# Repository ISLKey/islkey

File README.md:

# ISLKey

Access-control platform by **ISL Technologies** — ESP32-based door controllers with a
Windows flasher/commissioning tool and a companion mobile app.

## Repository layout

| Path | What it is | Stack |
|------|-----------|-------|
| `islkey-firmware/` | Door-controller firmware — 4 board targets (relay-board, devkit, ttgo, wt32-eth01). Inputs (exit/door/fire/tamper), relay-driven lock, cloud HMAC device-auth, NimBLE. | ESP32 / PlatformIO / Arduino |
| `islkey-flasher/`  | Desktop flasher + serial commissioning tool. Flashes merged full-flash images at `0x0`, assigns serials, writes WiFi/API config over serial. | Electron / Node.js |
| `islkey-app/`      | Companion door-access mobile app (NFC tap → resolve → unlock). | Flutter |
| `kicad/`           | KiCad 8 schematic for the TTGO controller (inputs, relay lock output, monitored fire link, backup power). | KiCad |
| `wordpress/`       | Drop-in integration notes for the isl-key WordPress plugin (device API / provisioning). | — |
| `make_wiring_diagram.py` | Generates the 4-sheet wiring/pinout PDF (`ISLKey-Wiring-Diagram.pdf`). | Python / matplotlib |
| `make_kicad_schematic.py` | Generates `kicad/ISLKey.kicad_sch` from source. | Python |

## Building

- **Firmware:** `cd islkey-firmware && python -m platformio run` (per-env in `platformio.ini`).
  After a rebuild, regenerate the merged images with `esptool merge_bin` (see below) — the
  flasher writes a **merged full-flash image at `0x0`**; a raw app image boot-loops the board.
- **Flasher:** `cd islkey-flasher && npm install && npm start` (or `npm run build` for the installer).
- **App:** `cd islkey-app && flutter pub get && flutter run`.

## Hardware notes

- On the **TTGO T-Display** target the TFT occupies GPIO 4/5/16/18/19/23, so door I/O is
  remapped: inputs GPIO 13/25/26/27, relays GPIO 32/33.
- The lock is switched via an **external opto-isolated relay module** (COM/NC), with a
  single **volt-free fire N/C contact in series** (hardware release, controller-independent)
  that is **opto-monitored to GPIO26** for fire detection + cable supervision. See `kicad/`
  and the wiring PDF.

## Not in this repo

Build artifacts (`.pio/`, `node_modules/`, Flutter `build/`, installer `dist/`) and
**operational secrets** — the per-device serial register / AP passwords (`islkey-flasher/serials/`)
and any real `.islkey` provisioning configs — are git-ignored.

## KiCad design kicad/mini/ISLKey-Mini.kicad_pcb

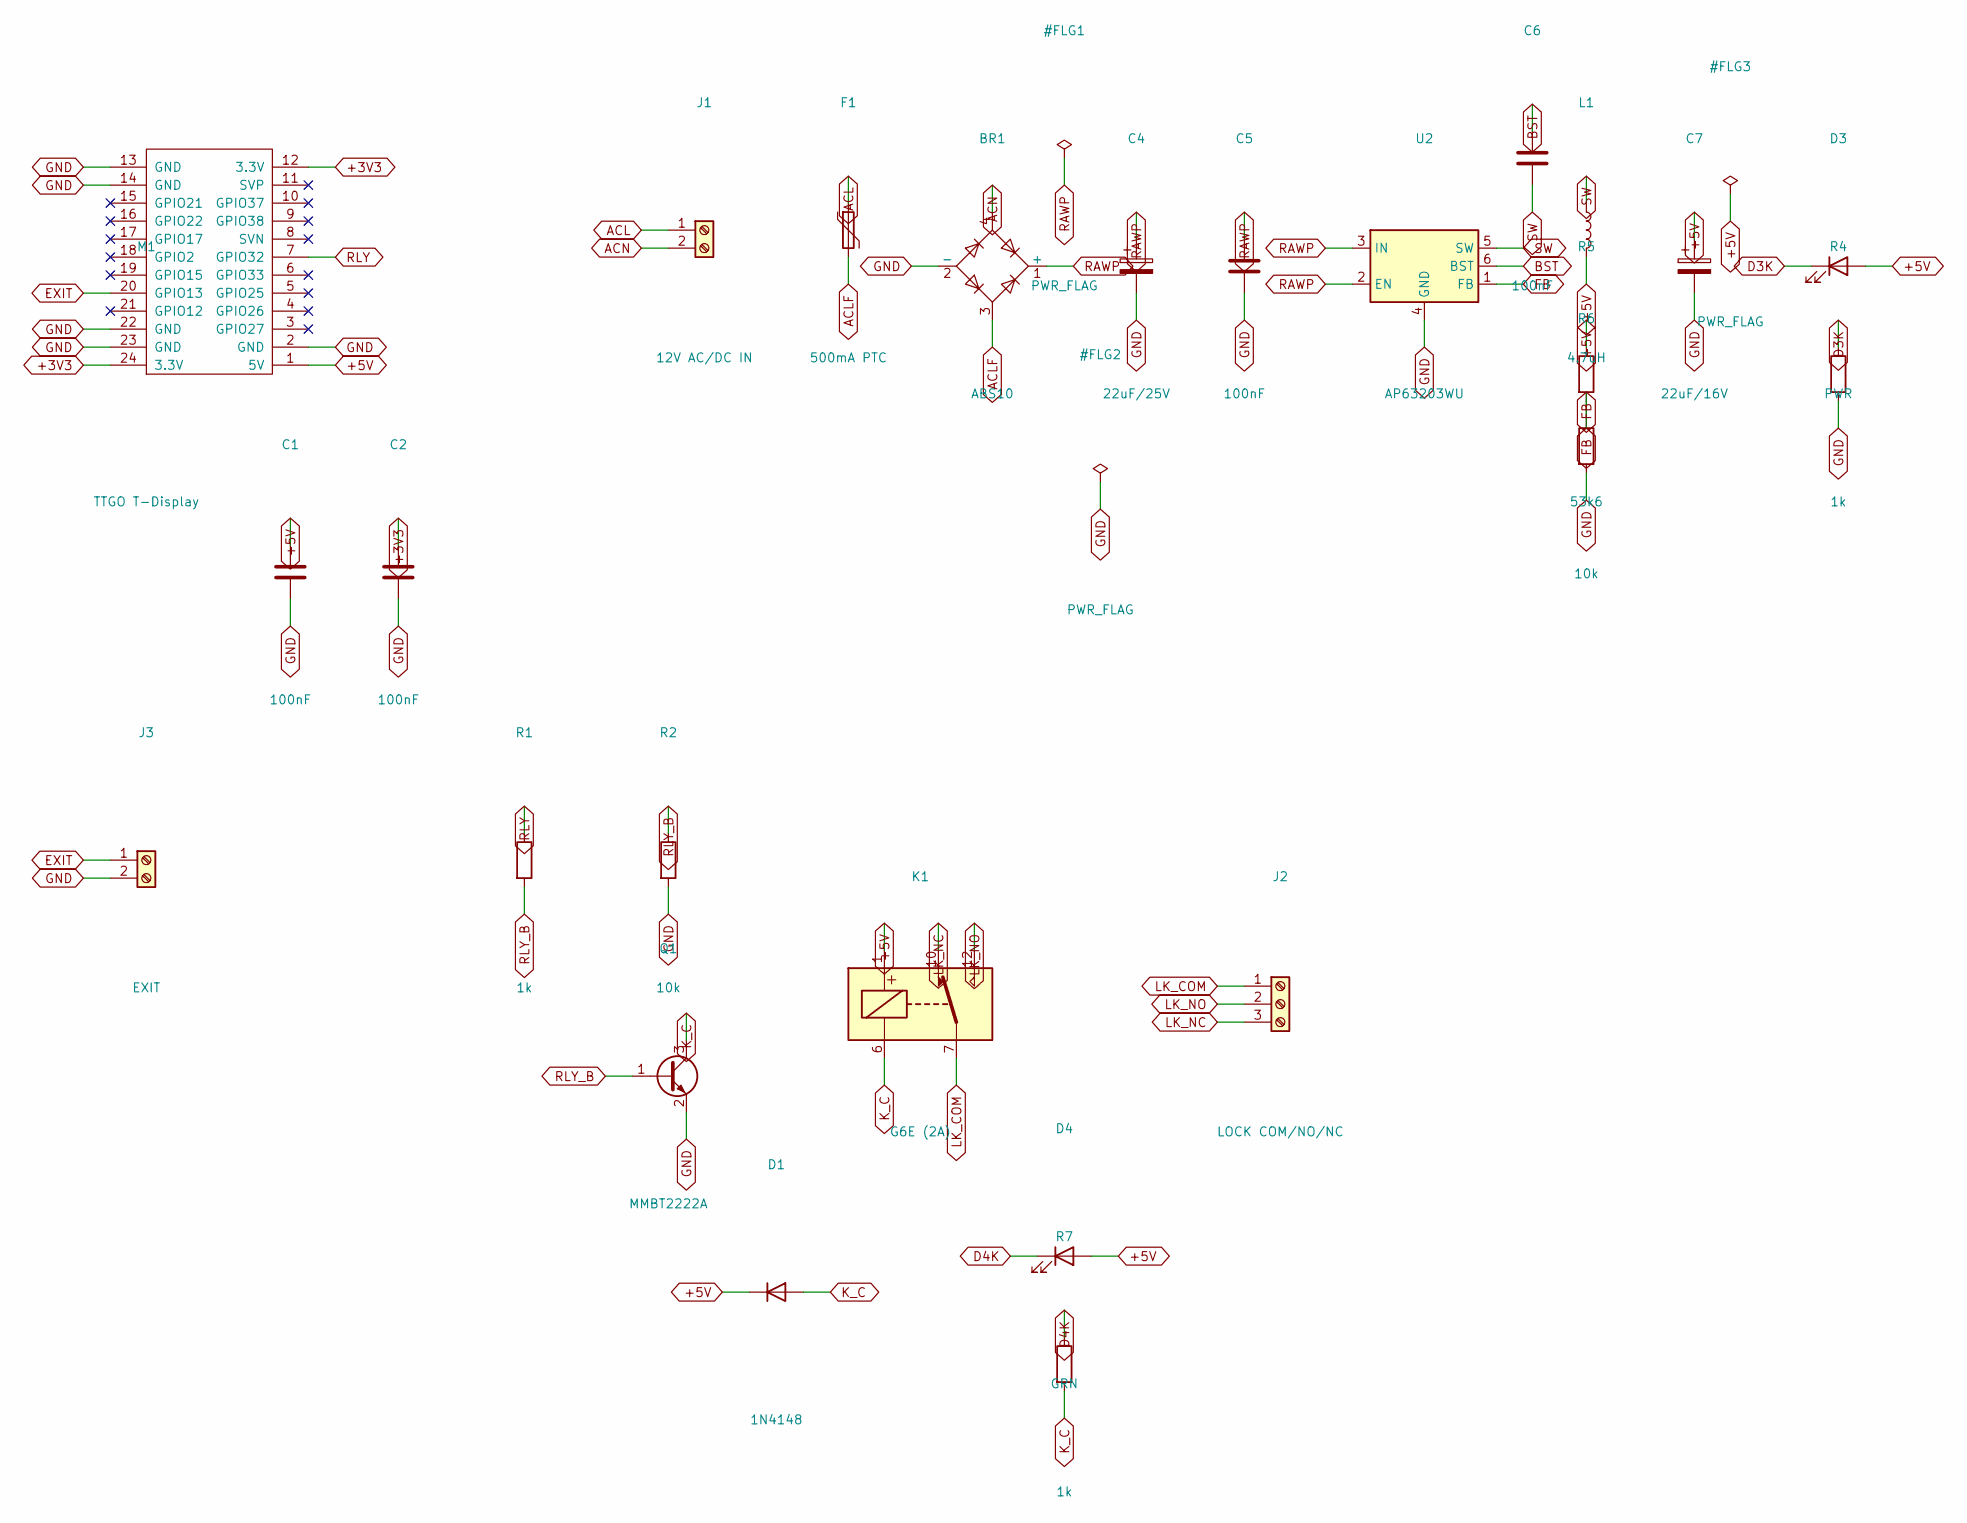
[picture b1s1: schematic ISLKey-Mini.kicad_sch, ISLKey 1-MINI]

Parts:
BR1: ABS10; Diode_Bridge_Diotec_ABS
C1, C2, C5, C6: 100nF; C_0805_2012Metric
C4: 22uF/25V; CP_Elec_6.3x5.3
C7: 22uF/16V; CP_Elec_6.3x5.3
D1: 1N4148; D_SOD-123
D3: PWR; LED_0805_2012Metric
D4: GRN; LED_0805_2012Metric
F1: 500mA PTC; Fuse_1812_4532Metric
J1: 12V AC/DC IN; TerminalBlock_Phoenix_PT-1,5-2-3.5-H_1x02_P3.50mm_Horizontal
J2: LOCK COM/NO/NC; TerminalBlock_Phoenix_PT-1,5-3-3.5-H_1x03_P3.50mm_Horizontal
J3: EXIT; TerminalBlock_Phoenix_PT-1,5-2-3.5-H_1x02_P3.50mm_Horizontal
K1: G6E (2A); Relay_SPDT_Omron_G6E
L1: 4.7uH; L_6.3x6.3_H3
M1: TTGO T-Display; TTGO_ESP32_TDisplay_v1.1
Q1: MMBT2222A; SOT-23
R1, R4, R7: 1k; R_0805_2012Metric
R2, R6: 10k; R_0805_2012Metric
R5: 53k6; R_0805_2012Metric
U2: AP63203WU; TSOT-23-6

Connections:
+3V3: C2.1, M1.12 (3.3V), M1.24 (3.3V)
+5V: C1.1, C7.1, D1.1 (K), D3.2 (A), D4.2 (A), K1.1, L1.2, M1.1 (5V), R5.1
ACL: F1.1, J1.1
ACLF: BR1.3, F1.2
ACN: BR1.4, J1.2
BST: C6.1, U2.6 (BST)
D3K: D3.1 (K), R4.1
D4K: D4.1 (K), R7.1
EXIT: J3.1, M1.20 (GPIO13)
FB: R5.2, R6.1, U2.1 (FB)
GND: BR1.2 (-), C1.2, C2.2, C4.2, C5.2, C7.2, J3.2, M1.2 (GND), M1.13 (GND), M1.14 (GND), M1.22 (GND), M1.23 (GND), Q1.2 (E), R2.2, R4.2, R6.2, U2.4 (GND)
K_C: D1.2 (A), K1.6, Q1.3 (C), R7.2
LK_COM: J2.1, K1.7
LK_NC: J2.3, K1.10
LK_NO: J2.2, K1.12
RAWP: BR1.1 (+), C4.1, C5.1, U2.2 (EN), U2.3 (IN)
RLY: M1.7 (GPIO32), R1.1
RLY_B: Q1.1 (B), R1.2, R2.1
SW: C6.2, L1.1, U2.5 (SW)

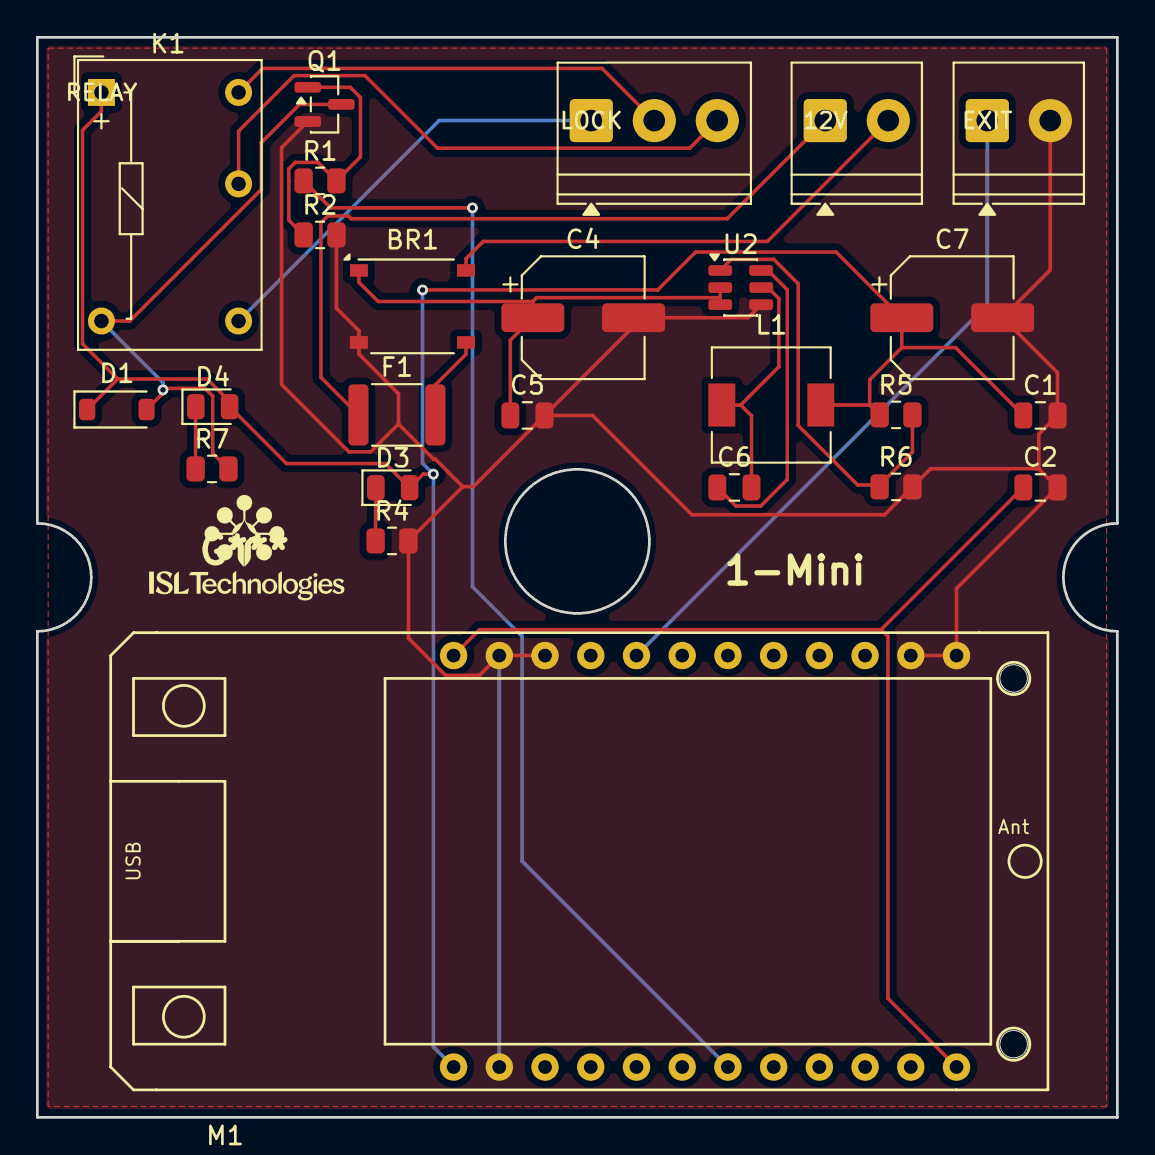
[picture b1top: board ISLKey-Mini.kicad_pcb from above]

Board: 2 copper layers, 60.0 x 60.0 mm, 25 parts (0 on the bottom side), 19 nets.

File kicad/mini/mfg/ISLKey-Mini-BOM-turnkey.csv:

Item,Refs,Qty,Value,Footprint,Type,Manufacturer,MPN,Distributor,Notes
1,"R1,R4,R7",3,1k,R_0805,SMD,Yageo,RC0805FR-071KL,LCSC C17513,
2,"R2,R6",2,10k,R_0805,SMD,Yageo,RC0805FR-0710KL,LCSC C17414,
3,"R5",1,53.6k,R_0805,SMD,Yageo,RC0805FR-0753K6L,Digikey,"buck FB divider (5V out)"
4,"C1,C2,C5,C6",4,100nF,C_0805,SMD,Samsung,CL21B104KBCNNNC,LCSC C1525,50V X7R
5,"C4",1,22uF 25V,CP_Elec_6.3x5.3,SMD,Panasonic,EEE-1EA220P,Digikey,SMD alu 6.3mm (bridge bulk)
6,"C7",1,22uF 16V,CP_Elec_6.3x5.3,SMD,Panasonic,EEE-1CA220P,Digikey,SMD alu 6.3mm (5V out)
7,"L1",1,4.7uH,L_6.3x6.3,SMD,Sunlord,SWPA6045S4R7MT,LCSC C167218,">=2A shielded power inductor"
8,"U2",1,AP63203WU,TSOT-23-6,SMD,Diodes Inc,AP63203WU-7,Digikey,"3.8-32V -> 5V 2A buck"
9,"BR1",1,ABS10,Diode_Bridge_Diotec_ABS,SMD,Diotec,ABS10,LCSC,"1A 1000V SMD bridge (AC or DC in)"
10,"F1",1,500mA PTC,Fuse_1812,SMD,Bourns,MF-MSMF050-2,Digikey,resettable PTC 1812
11,"D1",1,1N4148,SOD-123,SMD,Diodes Inc,1N4148W-7-F,LCSC C81598,relay flyback
12,"Q1",1,MMBT2222A,SOT-23,SMD,onsemi,MMBT2222ALT1G,LCSC C8286,relay driver
13,"D3",1,PWR (red),LED_0805,SMD,Kingbright,APT2012SURCK,LCSC C2286,power LED
14,"D4",1,GRN,LED_0805,SMD,Kingbright,APT2012LZGCK,LCSC C72043,relay-status LED
15,"K1",1,G6E (2A),Relay_SPDT_Omron_G6E,THT,Omron,G6E-134P-ST-US DC5,Digikey,"5V coil SPDT 2A - NOTE order the DC5 (5V) coil variant"
16,"J1,J3",2,Term 2-pin,"PT-1,5/2-3.5-H",THT,Phoenix Contact,"PT 1,5/2-3,5-H (1935161)",Digikey,"3.5mm horizontal-entry low-profile"
17,"J2",1,Term 3-pin,"PT-1,5/3-3.5-H",THT,Phoenix Contact,"PT 1,5/3-3,5-H (1935174)",Digikey,"3.5mm horizontal-entry low-profile"
NOTE,,,,,,,,,"M1 (TTGO T-Display) omitted - customer-sourced, fits headers post-assembly. K1: order the 5V-coil G6E. Phoenix order nos. indicative - confirm the PT-H horizontal variant. Distributor PNs indicative - confirm stock before ordering."

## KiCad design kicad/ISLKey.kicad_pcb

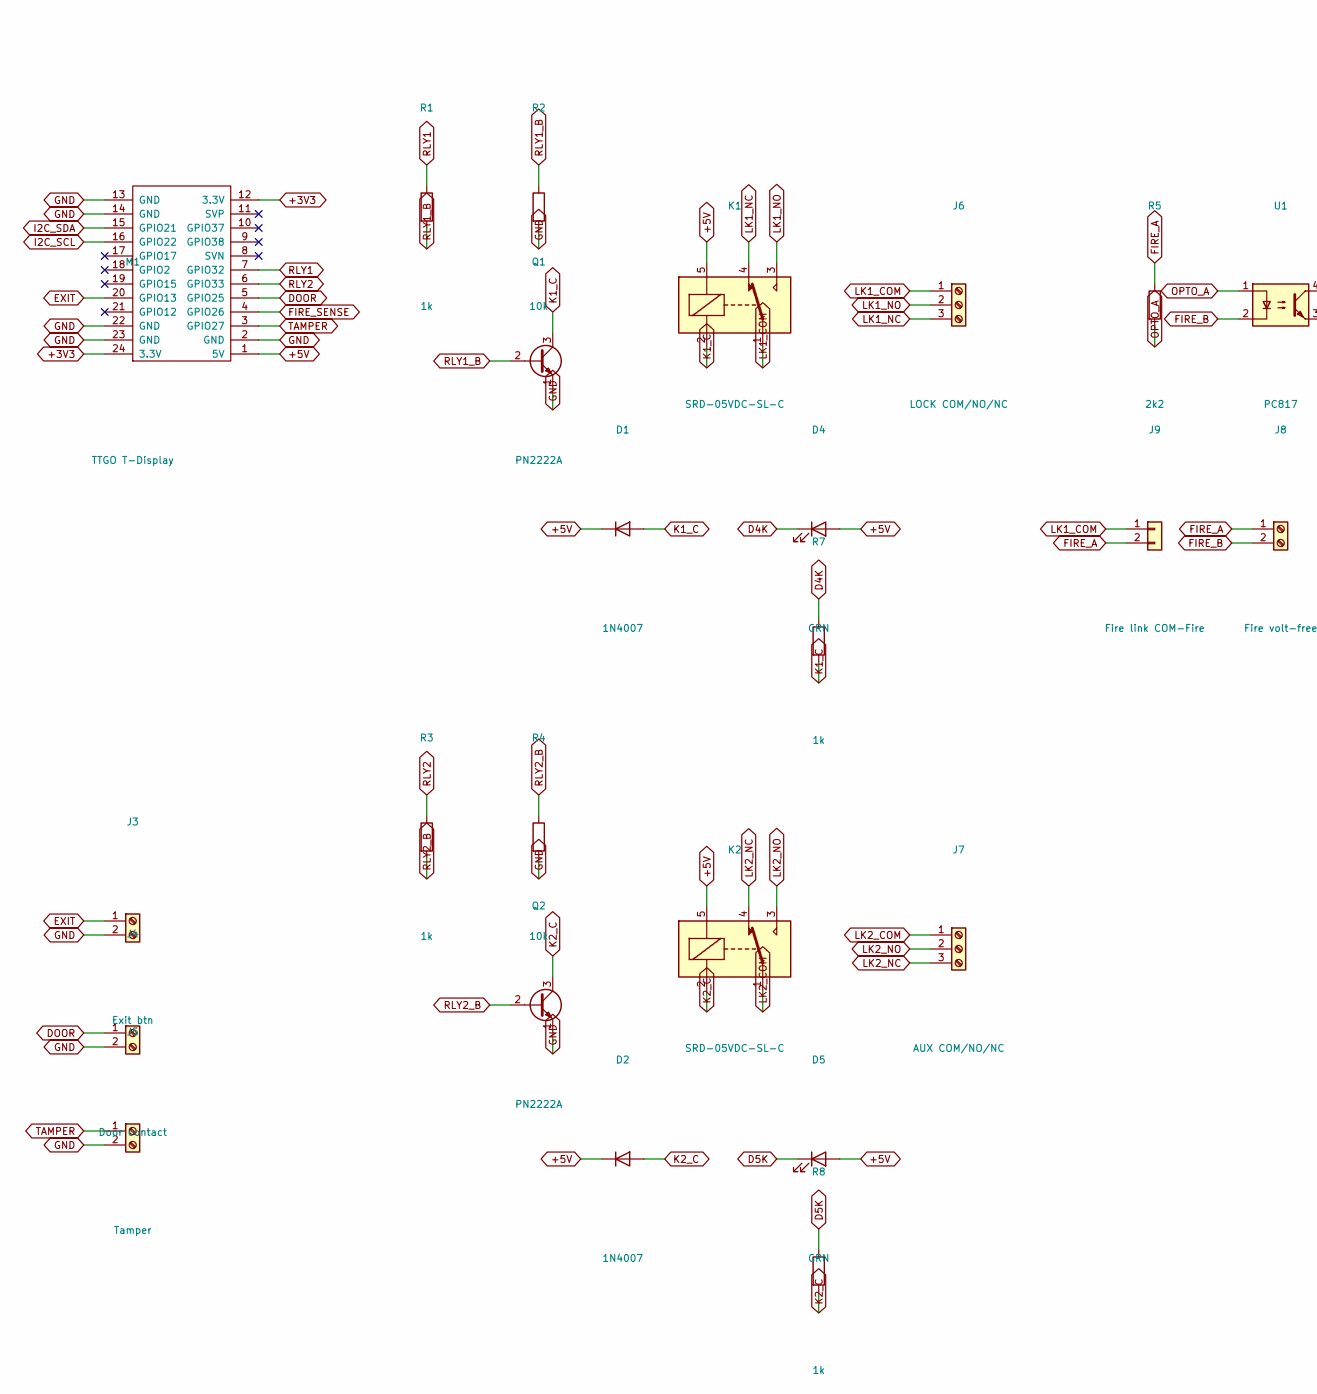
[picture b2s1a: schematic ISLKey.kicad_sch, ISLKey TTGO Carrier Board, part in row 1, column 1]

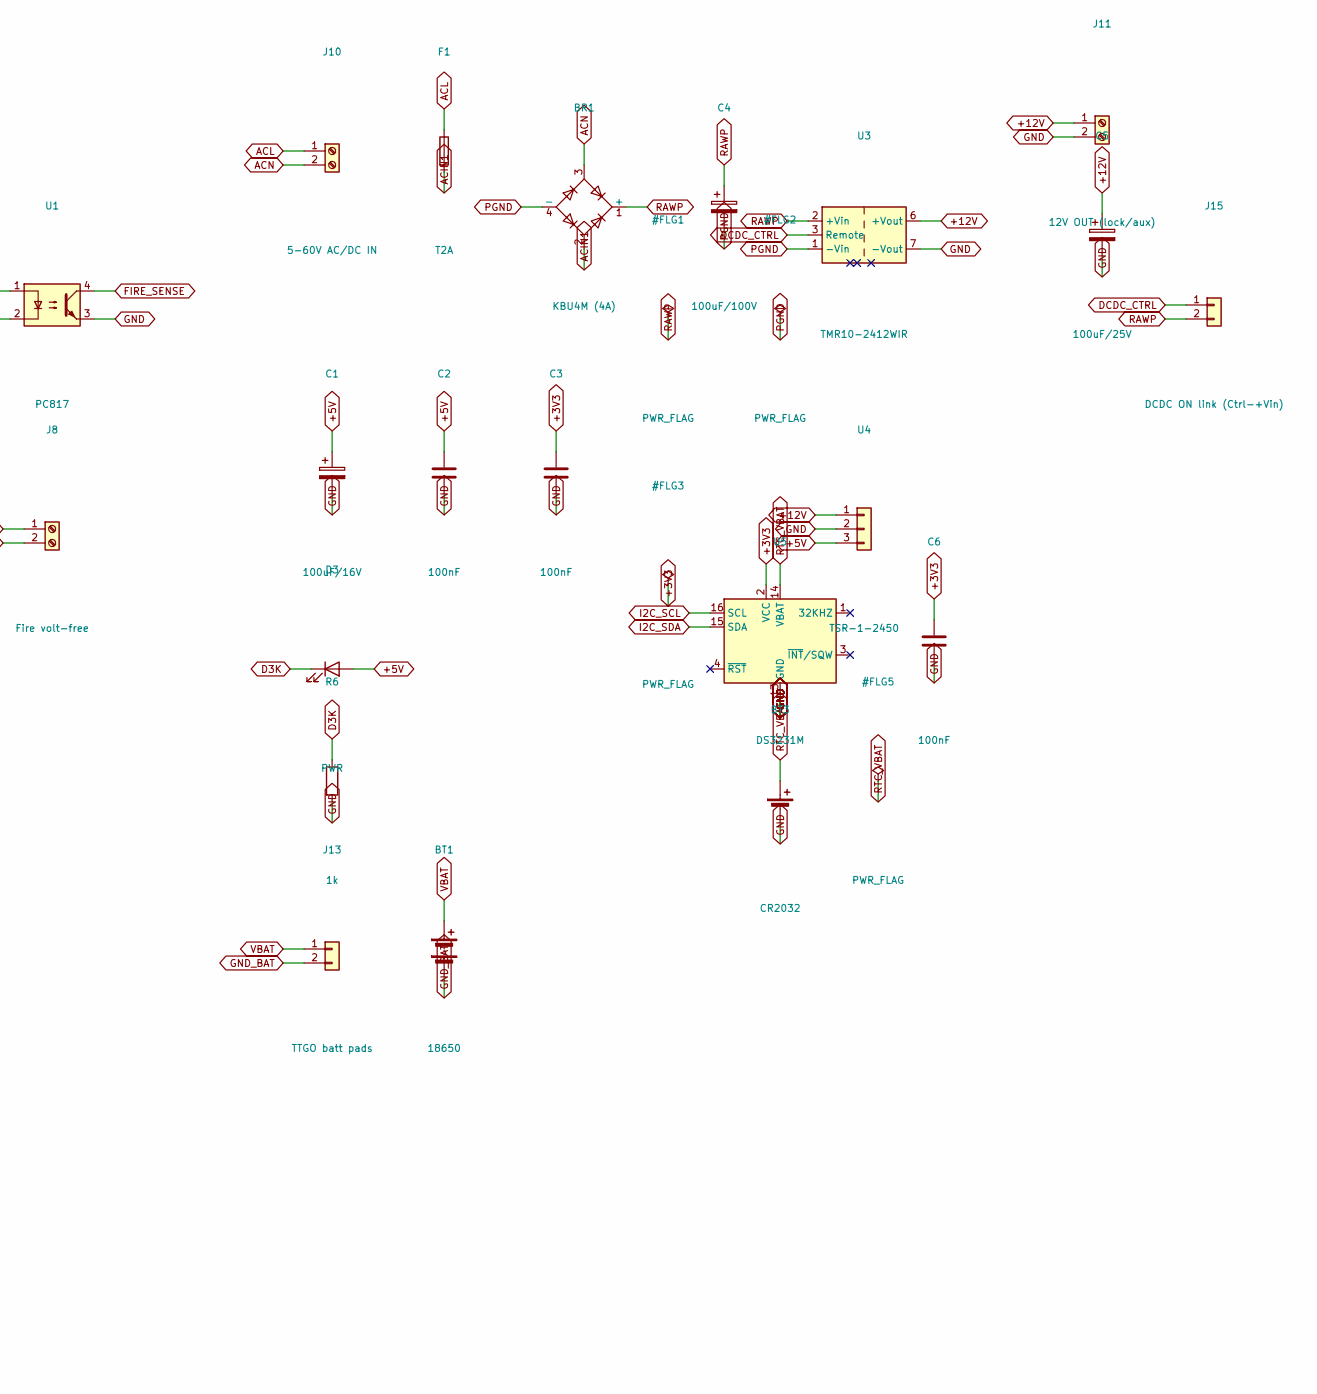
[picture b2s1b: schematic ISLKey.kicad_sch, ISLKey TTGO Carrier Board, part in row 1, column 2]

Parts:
BR1: KBU4M (4A); Diode_Bridge_Vishay_KBU
BT1: 18650; BatteryHolder_Keystone_1042_1x18650
BT3: CR2032; BatteryHolder_Keystone_3002_1x2032
C1: 100uF/16V; CP_Elec_6.3x5.3
C2, C3, C6: 100nF; C_0805_2012Metric
C4: 100uF/100V; CP_Elec_10x10.5
C5: 100uF/25V; CP_Elec_6.3x5.3
D1, D2: 1N4007; D_SMA
D3: PWR; LED_0805_2012Metric
D4, D5: GRN; LED_0805_2012Metric
F1: T2A; Fuseholder_Clip-5x20mm_Keystone_3512_Inline_P23.62x7.27mm_D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
J3: Exit btn; TerminalBlock_Phoenix_MKDS-1,5-2-5.08_1x02_P5.08mm_Horizont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
J4: Door contact; TerminalBlock_Phoenix_MKDS-1,5-2-5.08_1x02_P5.08mm_Horizont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
J5: Tamper; TerminalBlock_Phoenix_MKDS-1,5-2-5.08_1x02_P5.08mm_Horizont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
J6: LOCK COM/NO/NC; TerminalBlock_Phoenix_MKDS-1,5-3-5.08_1x03_P5.08mm_Horizont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
J7: AUX COM/NO/NC; TerminalBlock_Phoenix_MKDS-1,5-3-5.08_1x03_P5.08mm_Horizont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
J8: Fire volt-free; TerminalBlock_Phoenix_MKDS-1,5-2-5.08_1x02_P5.08mm_Horizont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
J9: Fire link COM-Fire; PinHeader_1x02_P2.54mm_Vertical
J10: 5-60V AC/DC IN; TerminalBlock_Phoenix_MKDS-3-2-5.08_1x02_P5.08mm_Horizontal
J11: 12V OUT (lock/aux); TerminalBlock_Phoenix_MKDS-3-2-5.08_1x02_P5.08mm_Horizontal
J13: TTGO batt pads; PinHeader_1x02_P2.54mm_Vertical
J15: DCDC ON link (Ctrl-+Vin); PinHeader_1x02_P2.54mm_Vertical
K1, K2: SRD-05VDC-SL-C; Relay_SPDT_SANYOU_SRD_Series_Form_C
M1: TTGO T-Display; TTGO_ESP32_TDisplay_v1.1
Q1, Q2: PN2222A; TO-92_Inline
R1, R3, R6, R7, R8: 1k; R_0805_2012Metric
R2, R4: 10k; R_0805_2012Metric
R5: 2k2; R_0805_2012Metric
U1: PC817; DIP-4_W7.62mm
U3: TMR10-2412WIR; Converter_DCDC_TRACO_TMR10-24xxWIR_48xxWIR_72xxWIR_THT
U4: TSR-1-2450; Converter_DCDC_TRACO_TSR-1_THT
U5: DS3231M; SOIC-16W_7.5x10.3mm_P1.27mm

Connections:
+3V3: C3.1, C6.1, M1.12 (3.3V), M1.24 (3.3V), U5.2 (VCC)
+5V: C1.1, C2.1, D1.1 (K), D2.1 (K), D3.2 (A), D4.2 (A), D5.2 (A), K1.5, K2.5, M1.1 (5V), U4.3
+12V: C5.1, J11.1, U3.6 (+Vout), U4.1
ACIN1: BR1.2, F1.2
ACL: F1.1, J10.1
ACN: BR1.3, J10.2
D3K: D3.1 (K), R6.1
D4K: D4.1 (K), R7.1
D5K: D5.1 (K), R8.1
DCDC_CTRL: J15.1, U3.3 (Remote)
DOOR: J4.1, M1.5 (GPIO25)
EXIT: J3.1, M1.20 (GPIO13)
FIRE_A: J8.1, J9.2, R5.1
FIRE_B: J8.2, U1.2
FIRE_SENSE: M1.4 (GPIO26), U1.4
GND: BT3.2 (-), C1.2, C2.2, C3.2, C5.2, C6.2, J3.2, J4.2, J5.2, J11.2, M1.2 (GND), M1.13 (GND), M1.14 (GND), M1.22 (GND), M1.23 (GND), Q1.1 (E), Q2.1 (E), R2.2, R4.2, R6.2, U1.3, U3.7 (-Vout), U4.2, U5.5 (GND), U5.6 (GND), U5.7 (GND), U5.8 (GND), U5.9 (GND), U5.10 (GND), U5.11 (GND), U5.12 (GND), U5.13 (GND)
GND_BAT: BT1.2 (-), J13.2
I2C_SCL: M1.16 (GPIO22), U5.16 (SCL)
I2C_SDA: M1.15 (GPIO21), U5.15 (SDA)
K1_C: D1.2 (A), K1.2, Q1.3 (C), R7.2
K2_C: D2.2 (A), K2.2, Q2.3 (C), R8.2
LK1_COM: J6.1, J9.1, K1.1
LK1_NC: J6.3, K1.4
LK1_NO: J6.2, K1.3
LK2_COM: J7.1, K2.1
LK2_NC: J7.3, K2.4
LK2_NO: J7.2, K2.3
OPTO_A: R5.2, U1.1
PGND: BR1.4 (-), C4.2, U3.1 (-Vin)
RAWP: BR1.1 (+), C4.1, J15.2, U3.2 (+Vin)
RLY1: M1.7 (GPIO32), R1.1
RLY1_B: Q1.2 (B), R1.2, R2.1
RLY2: M1.6 (GPIO33), R3.1
RLY2_B: Q2.2 (B), R3.2, R4.1
RTC_VBAT: BT3.1 (+), U5.14 (VBAT)
TAMPER: J5.1, M1.3 (GPIO27)
VBAT: BT1.1 (+), J13.1

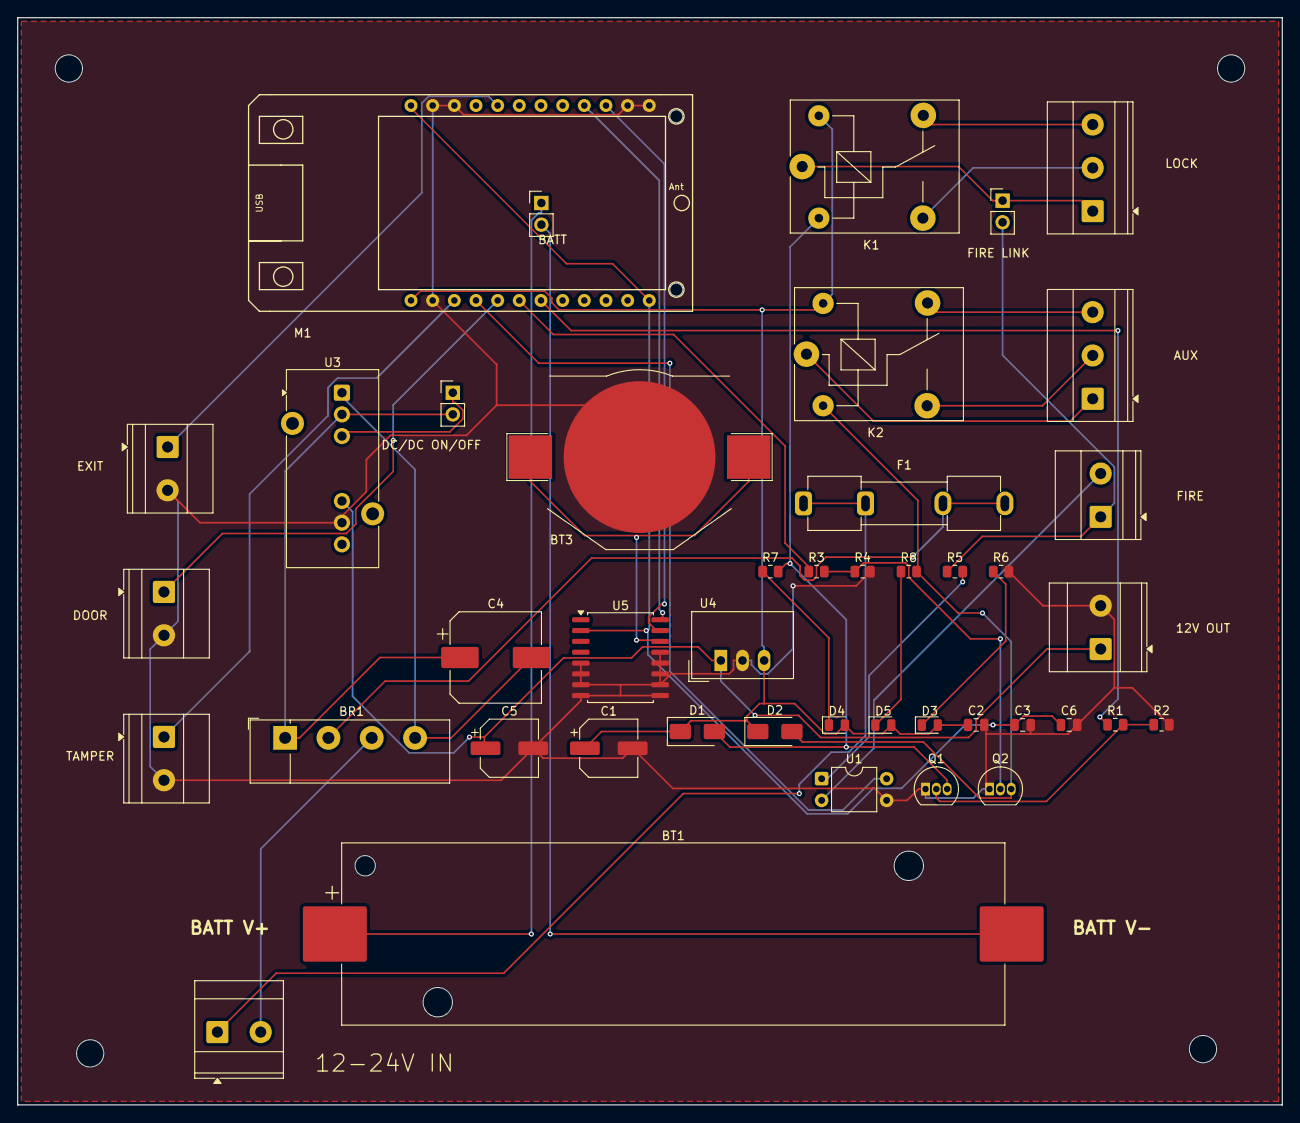
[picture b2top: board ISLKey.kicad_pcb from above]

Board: 2 copper layers, 148.3 x 127.5 mm, 47 parts (0 on the bottom side), 37 nets.

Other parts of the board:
H1, H2, H3, H4: MountingHole_3.2mm_M3

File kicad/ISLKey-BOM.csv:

"Refs","Value","Footprint","Qty"
"BR1","KBU4M (4A)","Diode_THT:Diode_Bridge_Vishay_KBU","1"
"BT1","18650","Battery:BatteryHolder_Keystone_1042_1x18650","1"
"BT3","CR2032","Battery:BatteryHolder_Keystone_3002_1x2032","1"
"C1","100uF/16V","Capacitor_SMD:CP_Elec_6.3x5.3","1"
"C2,C3,C6","100nF","Capacitor_SMD:C_0805_2012Metric","3"
"C4","100uF/100V","Capacitor_SMD:CP_Elec_10x10.5","1"
"C5","100uF/25V","Capacitor_SMD:CP_Elec_6.3x5.3","1"
"D1,D2","1N4007","Diode_SMD:D_SMA","2"
"D3","PWR","LED_SMD:LED_0805_2012Metric","1"
"D4,D5","GRN","LED_SMD:LED_0805_2012Metric","2"
"F1","T2A","Fuse:Fuseholder_Clip-5x20mm_Keystone_3512_Inline_P23.62x7.27mm_D1.02x1.57mm_Horizontal","1"
"J3","Exit btn","TerminalBlock_Phoenix:TerminalBlock_Phoenix_MKDS-1,5-2-5.08_1x02_P5.08mm_Horizontal","1"
"J4","Door contact","TerminalBlock_Phoenix:TerminalBlock_Phoenix_MKDS-1,5-2-5.08_1x02_P5.08mm_Horizontal","1"
"J5","Tamper","TerminalBlock_Phoenix:TerminalBlock_Phoenix_MKDS-1,5-2-5.08_1x02_P5.08mm_Horizontal","1"
"J6","LOCK COM/NO/NC","TerminalBlock_Phoenix:TerminalBlock_Phoenix_MKDS-1,5-3-5.08_1x03_P5.08mm_Horizontal","1"
"J7","AUX COM/NO/NC","TerminalBlock_Phoenix:TerminalBlock_Phoenix_MKDS-1,5-3-5.08_1x03_P5.08mm_Horizontal","1"
"J8","Fire volt-free","TerminalBlock_Phoenix:TerminalBlock_Phoenix_MKDS-1,5-2-5.08_1x02_P5.08mm_Horizontal","1"
"J9","Fire link COM-Fire","Connector_PinHeader_2.54mm:PinHeader_1x02_P2.54mm_Vertical","1"
"J10","5-60V AC/DC IN","TerminalBlock_Phoenix:TerminalBlock_Phoenix_MKDS-3-2-5.08_1x02_P5.08mm_Horizontal","1"
"J11","12V OUT (lock/aux)","TerminalBlock_Phoenix:TerminalBlock_Phoenix_MKDS-3-2-5.08_1x02_P5.08mm_Horizontal","1"
"J13","TTGO batt pads","Connector_PinHeader_2.54mm:PinHeader_1x02_P2.54mm_Vertical","1"
"J15","DCDC ON link (Ctrl-+Vin)","Connector_PinHeader_2.54mm:PinHeader_1x02_P2.54mm_Vertical","1"
"K1,K2","SRD-05VDC-SL-C","Relay_THT:Relay_SPDT_SANYOU_SRD_Series_Form_C","2"
"M1","TTGO T-Display","ISLKey:TTGO_ESP32_TDisplay_v1.1","1"
"Q1,Q2","PN2222A","Package_TO_SOT_THT:TO-92_Inline","2"
"R1,R3,R6-R8","1k","Resistor_SMD:R_0805_2012Metric","5"
"R2,R4","10k","Resistor_SMD:R_0805_2012Metric","2"
"R5","2k2","Resistor_SMD:R_0805_2012Metric","1"
"U1","PC817","Package_DIP:DIP-4_W7.62mm","1"
"U3","TMR10-2412WIR","Converter_DCDC:Converter_DCDC_TRACO_TMR10-24xxWIR_48xxWIR_72xxWIR_THT","1"
"U4","TSR-1-2450","Converter_DCDC:Converter_DCDC_TRACO_TSR-1_THT","1"
"U5","DS3231M","Package_SO:SOIC-16W_7.5x10.3mm_P1.27mm","1"

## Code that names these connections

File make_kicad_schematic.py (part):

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
# ── define the symbols used ───────────────────────────────────────────────────
def_symbol("ESP32_TTGO", 17.78,
           left=[("GPIO13", "EXIT"), ("GPIO25", "DOOR"), ("GPIO26", "FIRE"), ("GPIO27", "TAMPER")],
           right=[("GPIO32", "IN1"), ("GPIO33", "IN2"), ("5V", "+5V"), ("GND", "GND")],
           etype="bidirectional")
def_symbol("Relay_2Ch", 15.24,
           left=[("IN1", "IN1"), ("IN2", "IN2"), ("VCC", "+5V"), ("GND", "GND")],
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place("Diode_1N4007","D1",  "1N4007 flyback",    300, 148)
place("Fire_Contact","J5",  "Fire volt-free N/C (series, opens on fire)", 372, 108)
place("R_Opto",      "R1",  "2k2 opto LED series", 372, 88)
place("Opto_PC817",  "U2",  "PC817 fire-link monitor -> GPIO26", 300, 78)
place("Mains_PSU",   "PS1", "5V Mains PSU",      110, 210)
place("UPS_18650",   "BT1", "2x18650 UPS 5V",    110, 235)

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
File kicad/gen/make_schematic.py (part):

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    # TTGO T-Display module (single 24-pad footprint; pad<->GPIO per GillesOdb lib)
    ("M1", "ISLKey:TTGO_ESP32_TDISPLAY_V1.1", "TTGO T-Display", 40, 100,
     {"7":"RLY1", "6":"RLY2", "5":"DOOR", "4":"FIRE_SENSE", "3":"TAMPER", "20":"EXIT",
      "15":"I2C_SDA", "16":"I2C_SCL",   # GPIO21/22 (onboard 10k pull-ups) -> RTC
      "1":"+5V", "12":"+3V3", "24":"+3V3",
      "2":"GND", "13":"GND", "14":"GND", "22":"GND", "23":"GND"}),

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    ("J4", "Connector:Screw_Terminal_01x02", "Door contact",40, 220, {"1":"DOOR","2":"GND"}),
    ("J5", "Connector:Screw_Terminal_01x02", "Tamper",      40, 240, {"1":"TAMPER","2":"GND"}),

    # Relay channel 1 (lock)  GPIO32
    ("R1", "Device:R", "1k",  95, 70, {"1":"RLY1","2":"RLY1_B"}),
    ("R2", "Device:R", "10k", 115,70, {"1":"RLY1_B","2":"GND"}),
    ("Q1", "Transistor_BJT:Q_NPN_EBC", "PN2222A", 115, 100, {"1":"GND","2":"RLY1_B","3":"K1_C"}),
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    ("R7", "Device:R", "1k", 165, 150, {"1":"D4K","2":"K1_C"}),
    ("J6","Connector:Screw_Terminal_01x03", "LOCK COM/NO/NC", 190, 90, {"1":"LK1_COM","2":"LK1_NO","3":"LK1_NC"}),

    # Relay channel 2 (aux)  GPIO33
    ("R3", "Device:R", "1k",  95, 185, {"1":"RLY2","2":"RLY2_B"}),
    ("R4", "Device:R", "10k", 115,185, {"1":"RLY2_B","2":"GND"}),
    ("Q2", "Transistor_BJT:Q_NPN_EBC", "PN2222A", 115, 215, {"1":"GND","2":"RLY2_B","3":"K2_C"}),
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    ("R8", "Device:R", "1k", 165, 265, {"1":"D5K","2":"K2_C"}),
    ("J7","Connector:Screw_Terminal_01x03", "AUX COM/NO/NC", 190, 205, {"1":"LK2_COM","2":"LK2_NO","3":"LK2_NC"}),

    # Fire interface (monitored series link)  GPIO26
    ("U1", "Isolator:PC817", "PC817", 250, 90, {"1":"OPTO_A","2":"FIRE_B","3":"GND","4":"FIRE_SENSE"}),
    ("R5", "Device:R", "2k2", 225, 90, {"1":"FIRE_A","2":"OPTO_A"}),
    ("J8","Connector:Screw_Terminal_01x02", "Fire volt-free", 250, 130, {"1":"FIRE_A","2":"FIRE_B"}),
    ("J9","Connector_Generic:Conn_01x02", "Fire link COM-Fire", 225, 130, {"1":"LK1_COM","2":"FIRE_A"}),
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    ("J13","Connector_Generic:Conn_01x02", "TTGO batt pads", 300, 205, {"1":"VBAT","2":"GND_BAT"}),
    ("BT1","Device:Battery", "18650", 320, 205, {"1":"VBAT","2":"GND_BAT"}),

    # RTC (DS3231M) on I2C GPIO21/22, CR2032-backed
    ("U5", "Timer_RTC:DS3231M", "DS3231M", 380, 150,
     {"2":"+3V3", "14":"RTC_VBAT", "15":"I2C_SDA", "16":"I2C_SCL",
      "5":"GND","6":"GND","7":"GND","8":"GND","9":"GND","10":"GND","11":"GND","12":"GND","13":"GND",
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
